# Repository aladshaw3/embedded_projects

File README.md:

## Personal Embedded Projects
Mono Repo for various personal embedded projects with my husband

This mono repo is strictly just for code development with a lot of boilerplate for helping
to write unit tests for the code. Does not include build instructions for specific devices.

Artwork by [Aavastt](https://www.instagram.com/aavastt/)

# Getting Started

(1) Initial Setup

```bash
make environment
make grab-submodules
```

NOTE: Not strictly required if you have an environment that is already setup. See build/setup.sh for recommendations

(2) Running unit tests

```bash
make unit-tests
```

or

```bash
make unit-test TEST={TEST_NAME}
```

(3) Checking formatting

```bash
make static-code-analysis
make lint-filename
make pre-commit
```

or

```bash
make all-checks
```

(3) Building API-Docs

```bash
make api-docs
```

# Contributing

## New code project under `projects` folder

(1) Start by creating new folder under `projects`

e.g.,
```
embedded_projects/
├── projects/
│   ├── ExampleProject/
│   └── NewProject/         # Add here
```

(2) Update the `projects/sources.cmake` and `include.cmake` files for new location

e.g., source.cmake
```
################# Add other project directories here #####################
include_sources(ExampleProject)
include_sources(NewProject)      # Add here
```

e.g., include.cmake
```
################# Add other project directories here #####################
include_directories(${SIL_DIR}/ExampleProject)
include_directories(${SIL_DIR}/NewProject)
```

(3) Adding subdirectories in your project

You can add any subdirectories to your new project folder. You will
then need to add another layer of a `sources.cmake` file to add the
new subdirectories to be discoverable by the unit testing and static
code analysis infrastructure

See `projects/ExampleProject` for an example.

(4) Adding source code

Each sub-folder should contain both the header file and source file together.
Each sub-folder that contains source files needs to also include a `sources.cmake`
file. This file should call an `add_sources` helper function to tell cmake what
source files to include in the builds.

e.g., `projects/ExampleProject/unit_tests/sources.cmake`
```
add_sources(test_builds.cpp)
add_sources(test_eigen.cpp)
```

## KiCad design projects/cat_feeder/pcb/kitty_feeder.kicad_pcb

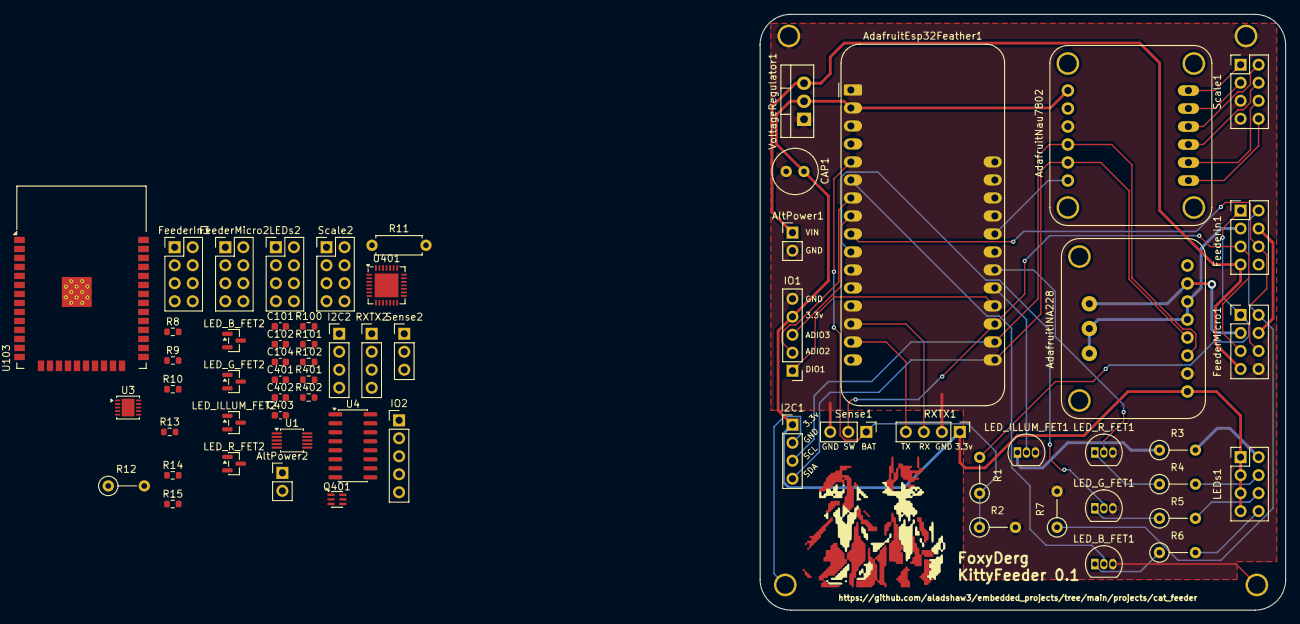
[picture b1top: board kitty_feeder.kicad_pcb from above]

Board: 2 copper layers, 74.2 x 84.1 mm, 63 parts (0 on the bottom side), 77 nets.

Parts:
AdafruitEsp32Feather1: Adafruit_Feather_Generic; Adafruit_Feather
AltPower1, AltPower2: Conn_01x02_Pin; PinHeader_1x02_P2.54mm_Vertical
C101: 22uF; C_0603_1608Metric
C102, C104, C401, C403: 100nF; C_0603_1608Metric
C402: 1uF; C_0603_1608Metric
CAP1: 100uf; C_Radial_D6.3mm_H11.0mm_P2.50mm
FeederIn1, FeederIn3: Conn_02x04_Odd_Even; PinHeader_2x04_P2.54mm_Vertical
FeederMicro1, FeederMicro2: Conn_02x04_Odd_Even; PinHeader_2x04_P2.54mm_Vertical
I2C1, I2C2: Conn_01x04_Pin; PinHeader_1x04_P2.54mm_Vertical
INA228: ina228_module
IO1, IO2: Conn_01x05_Pin; PinHeader_1x05_P2.54mm_Vertical
LED_B_FET1: BS170; TO-92_Inline
LED_B_FET2: BS170; SOT-23
LED_G_FET1: BS170; TO-92_Inline
LED_G_FET2: BS170; SOT-23
LED_ILLUM_FET1: BS170; TO-92_Inline
LED_ILLUM_FET2: BS170; SOT-23
LED_R_FET1: BS170; TO-92_Inline
LED_R_FET2: BS170; SOT-23
LEDs1, LEDs2: Conn_02x04_Odd_Even; PinHeader_2x04_P2.54mm_Vertical
Q401: MMDT3904; SOT-363_SC-70-6
R1, R2: 10kΩ; R_Axial_DIN0207_L6.3mm_D2.5mm_P5.08mm_Vertical
R3, R12: 0Ω; R_Axial_DIN0207_L6.3mm_D2.5mm_P5.08mm_Vertical
R4, R5, R6, R7: R; R_Axial_DIN0207_L6.3mm_D2.5mm_P5.08mm_Vertical
R8, R13, R14, R15: R; R_0603_1608Metric
R9, R10: 10kΩ; R_0603_1608Metric
R11: 15; R_Axial_DIN0207_L6.3mm_D2.5mm_P7.62mm_Horizontal
R100, R102: 100K; R_0603_1608Metric
R101, R401, R402: 10K; R_0603_1608Metric
RXTX1, RXTX2: Conn_01x04_Pin; PinHeader_1x04_P2.54mm_Vertical
Scale1, Scale2: Conn_02x04_Odd_Even; PinHeader_2x04_P2.54mm_Vertical
Sense1, Sense2: Conn_01x03_Pin; PinHeader_1x03_P2.54mm_Vertical
U1: INA228; TSSOP-10_3x3mm_P0.5mm
U2: nau7802_module
U3: HUSB238_xxxDD; WDFN-10-1EP_3x3mm_P0.5mm_EP1.8x2.5mm
U4: SOIC-16_3.9x9.9mm_P1.27mm
U103: ESP32-WROOM-32
U401: CP2102-GMR; QFN-28-1EP_5x5mm_P0.5mm_EP3.35x3.35mm
VoltageRegulator1: LD1117V33; TO-220-3_Vertical

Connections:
+3.3V: C101.1, C102.1, R101.1, U103.2 (VDD)
/kitty_feeder/3.3v: AdafruitEsp32Feather1.2 (3V3), CAP1.1, I2C1.1, INA228.1 (VIN), IO1.4, LEDs1.1, LEDs1.3, LEDs1.5, LEDs1.7, RXTX1.1, U2.1 (VIN), VoltageRegulator1.2 (VO)
/kitty_feeder/A+: Scale1.2, U2.9 (A+)
/kitty_feeder/A-: Scale1.4, U2.10 (A-)
/kitty_feeder/ADIO2: AdafruitEsp32Feather1.7 (A2), IO1.2
/kitty_feeder/ADIO3: AdafruitEsp32Feather1.8 (A3), IO1.3
/kitty_feeder/B+: Scale1.1, U2.7 (B+)
/kitty_feeder/B-: Scale1.3, U2.8 (B-)
/kitty_feeder/DIO1: AdafruitEsp32Feather1.20 (D1), IO1.1
/kitty_feeder/DRDY: AdafruitEsp32Feather1.24 (D5), U2.6 (DRDY)
/kitty_feeder/E+: Scale1.6, U2.11 (E+)
/kitty_feeder/E-: Scale1.8, U2.12 (E-)
/kitty_feeder/FeederBattery+: FeederIn1.2, FeederMicro1.2, R7.1
/kitty_feeder/FeederBattery-: FeederIn1.1, FeederMicro1.1, R1.2
/kitty_feeder/FeederBatterySense: AdafruitEsp32Feather1.5 (A0), R1.1, R2.1, Sense1.1
/kitty_feeder/FeederLimitSwitch+: AdafruitEsp32Feather1.9 (A4), FeederIn1.6, FeederMicro1.6
/kitty_feeder/FeederLimitSwitch-: AdafruitEsp32Feather1.19 (D0), FeederIn1.5, FeederMicro1.5, Sense1.2
/kitty_feeder/FeederVIN: AltPower1.1, FeederIn1.7, FeederMicro1.7, VoltageRegulator1.3 (VI)
/kitty_feeder/GND: AdafruitEsp32Feather1.4 (GND), AltPower1.2, CAP1.2, FeederIn1.8, FeederMicro1.8, I2C1.2, INA228.2 (GND), IO1.5, LED_B_FET1.3 (S), LED_G_FET1.3 (S), LED_ILLUM_FET1.3 (S), LED_R_FET1.3 (S), R2.2, R7.2, RXTX1.2, Scale1.5, Scale1.7, Sense1.3, U2.3 (GND), VoltageRegulator1.1 (GND)
/kitty_feeder/LED_B: LEDs1.8, R6.2
/kitty_feeder/LED_B_CONTROL: AdafruitEsp32Feather1.6 (A1), LED_B_FET1.2 (G)
/kitty_feeder/LED_G: LEDs1.6, R5.2
/kitty_feeder/LED_G_CONTROL: AdafruitEsp32Feather1.10 (A5), LED_G_FET1.2 (G)
/kitty_feeder/LED_ILLUM: LEDs1.2, R3.2
/kitty_feeder/LED_ILLUM_CONTROL: AdafruitEsp32Feather1.21 (D2), LED_ILLUM_FET1.2 (G)
/kitty_feeder/LED_R: LEDs1.4, R4.2
/kitty_feeder/LED_R_CONTROL: AdafruitEsp32Feather1.22 (D3), LED_R_FET1.2 (G)
/kitty_feeder/Motor+: FeederIn1.4, FeederMicro1.4
/kitty_feeder/Motor-: FeederMicro1.3, INA228.7 (FRONT_LOAD_VIN+), INA228.11 (BACK_LOAD_VIN+)
/kitty_feeder/Motor_Shunt-: FeederIn1.3, INA228.5 (FRONT_LOAD_VBUS), INA228.6 (FRONT_LOAD_VIN-), INA228.9 (BACK_LOAD_VIN-), INA228.10 (BACK_LOAD_VBUS)
/kitty_feeder/RX: AdafruitEsp32Feather1.14 (RX), RXTX1.3
/kitty_feeder/SCL: AdafruitEsp32Feather1.18 (SCL), I2C1.3, INA228.3 (SCL), U2.4 (SCL)
/kitty_feeder/SDA: AdafruitEsp32Feather1.17 (SDA), I2C1.4, INA228.4 (SDA), U2.5 (SDA)
/kitty_feeder/TX: AdafruitEsp32Feather1.15 (TX), RXTX1.4
/kitty_feeder_no_modules/3.3v: I2C2.1, IO2.4, LEDs2.1, LEDs2.3, LEDs2.5, LEDs2.7, R100.1, R102.1, RXTX2.1, U1.6 (VS), U4.1 (VIN)
/kitty_feeder_no_modules/A+: Scale2.2, U4.9 (A+)
/kitty_feeder_no_modules/A-: Scale2.4, U4.10 (A-)
/kitty_feeder_no_modules/B+: Scale2.1, U4.7 (B+)
/kitty_feeder_no_modules/B-: Scale2.3, U4.8 (B-)
/kitty_feeder_no_modules/DTR: Q401.4 (E2), R401.2, U401.28 (~DTR)
/kitty_feeder_no_modules/E+: Scale2.6, U4.11 (E+)
/kitty_feeder_no_modules/E-: Scale2.8, U4.12 (E-)
/kitty_feeder_no_modules/EN: C104.1, Q401.6 (C1), R101.2, U103.3 (EN)
/kitty_feeder_no_modules/FeederBattery+: FeederIn3.2, FeederMicro2.2, R8.1
/kitty_feeder_no_modules/FeederBattery-: FeederIn3.1, FeederMicro2.1, R9.2
/kitty_feeder_no_modules/FeederBatterySense: R9.1, R10.1, Sense2.1
/kitty_feeder_no_modules/FeederLimitSwitch+: FeederIn3.6, FeederMicro2.6
/kitty_feeder_no_modules/FeederLimitSwitch-: FeederIn3.5, FeederMicro2.5, Sense2.2
/kitty_feeder_no_modules/FeederVIN: AltPower2.1, FeederIn3.7, FeederMicro2.7
/kitty_feeder_no_modules/IO0: Q401.3 (C2), U103.25 (IO0)
/kitty_feeder_no_modules/LED_B: LEDs2.8, R15.2
/kitty_feeder_no_modules/LED_G: LEDs2.6, R14.2
/kitty_feeder_no_modules/LED_ILLUM: LEDs2.2, R12.2
/kitty_feeder_no_modules/LED_R: LEDs2.4, R13.2
/kitty_feeder_no_modules/Motor+: FeederIn3.4, FeederMicro2.4
/kitty_feeder_no_modules/Motor-: FeederMicro2.3, R11.2, U1.10 (Vin+)
/kitty_feeder_no_modules/Motor_Shunt-: FeederIn3.3, R11.1, U1.8 (Vbus), U1.9 (Vin-)
/kitty_feeder_no_modules/RTS: Q401.1 (E1), R402.2, U401.24 (~RTS)
/kitty_feeder_no_modules/RX: RXTX2.3, U103.34 (RXD0/IO3)
/kitty_feeder_no_modules/SCL: I2C2.3, U1.5 (SCL), U4.4 (SCL)
/kitty_feeder_no_modules/SDA: I2C2.4, U1.4 (SDA), U4.5 (SDA)
/kitty_feeder_no_modules/TX: RXTX2.4, U103.35 (TXD0/IO1)
/kitty_feeder_no_modules/VBUS: C402.1, C403.1, U401.7 (VREGIN), U401.8 (VBUS)
GND: AltPower2.2, C101.2, C102.2, C104.2, C401.2, C402.2, C403.2, FeederIn3.8, FeederMicro2.8, I2C2.2, IO2.5, LED_B_FET2.3 (S), LED_G_FET2.3 (S), LED_ILLUM_FET2.3 (S), LED_R_FET2.3 (S), R8.2, R10.2, RXTX2.2, Scale2.5, Scale2.7, Sense2.3, U1.7 (GND), U4.3 (GND), U103.1 (GND), U103.15 (GND), U103.38 (GND), U103.39 (GND), U401.3 (GND), U401.29 (GND)
unnamed: LED_B_FET1.1 (D), R6.1
unnamed: LED_B_FET2.1 (D), R15.1
unnamed: LED_G_FET1.1 (D), R5.1
unnamed: LED_G_FET2.1 (D), R14.1
unnamed: LED_ILLUM_FET1.1 (D), R3.1
unnamed: LED_ILLUM_FET2.1 (D), R12.1
unnamed: LED_R_FET1.1 (D), R4.1
unnamed: LED_R_FET2.1 (D), R13.1
unnamed: Q401.2 (B1), R401.1
unnamed: Q401.5 (B2), R402.1
unnamed: R102.2, U1.2 (A0)
unnamed: R100.2, U1.1 (A1)
unnamed: C401.1, U401.6 (VDD)
